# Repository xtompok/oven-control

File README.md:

# Oven control software
Boards and software used to control electric oven

# Installation

 - burn raspbian to SD card
 - create ssh file on boot partition of the SD card
 - `sudo raspi-config`
	- set hostname
	- set password
	- set locale
	- set timezone
	- set read-only
 - `sudo apt update`
 - `sudo apt install vim git python3-venv mosquitto nginx`
 - clone this repo
 - in `oven-control/sw/web_interface`:
	- `python3 -m venv venv`
	- `. venv/bin/activate/`
	- `pip install -r requirements.txt`
 - `mkdir -p .config/systemd/user/`
 - `cp oven_control.service .config/systemd/user/` 
 - `sudo loginctl enable-linger pi`
 - edit `/etc/mosquitto/mosquitto.conf`:

  log_dest stderr

  listener 1883
  protocol mqtt

  listener 9001
  protocol websockets

 - `sudo systemctl restart mosquitto`
 - edit `/etc/nginx/sites-available/default`
	- `root /home/pi/oven-control/sw/web_interface/static/`
 - edit `/etc/nginx/nginx.conf`:
	- add to `http` directive `charset UTF-8;`
 - `sudo systemctl restart nginx`

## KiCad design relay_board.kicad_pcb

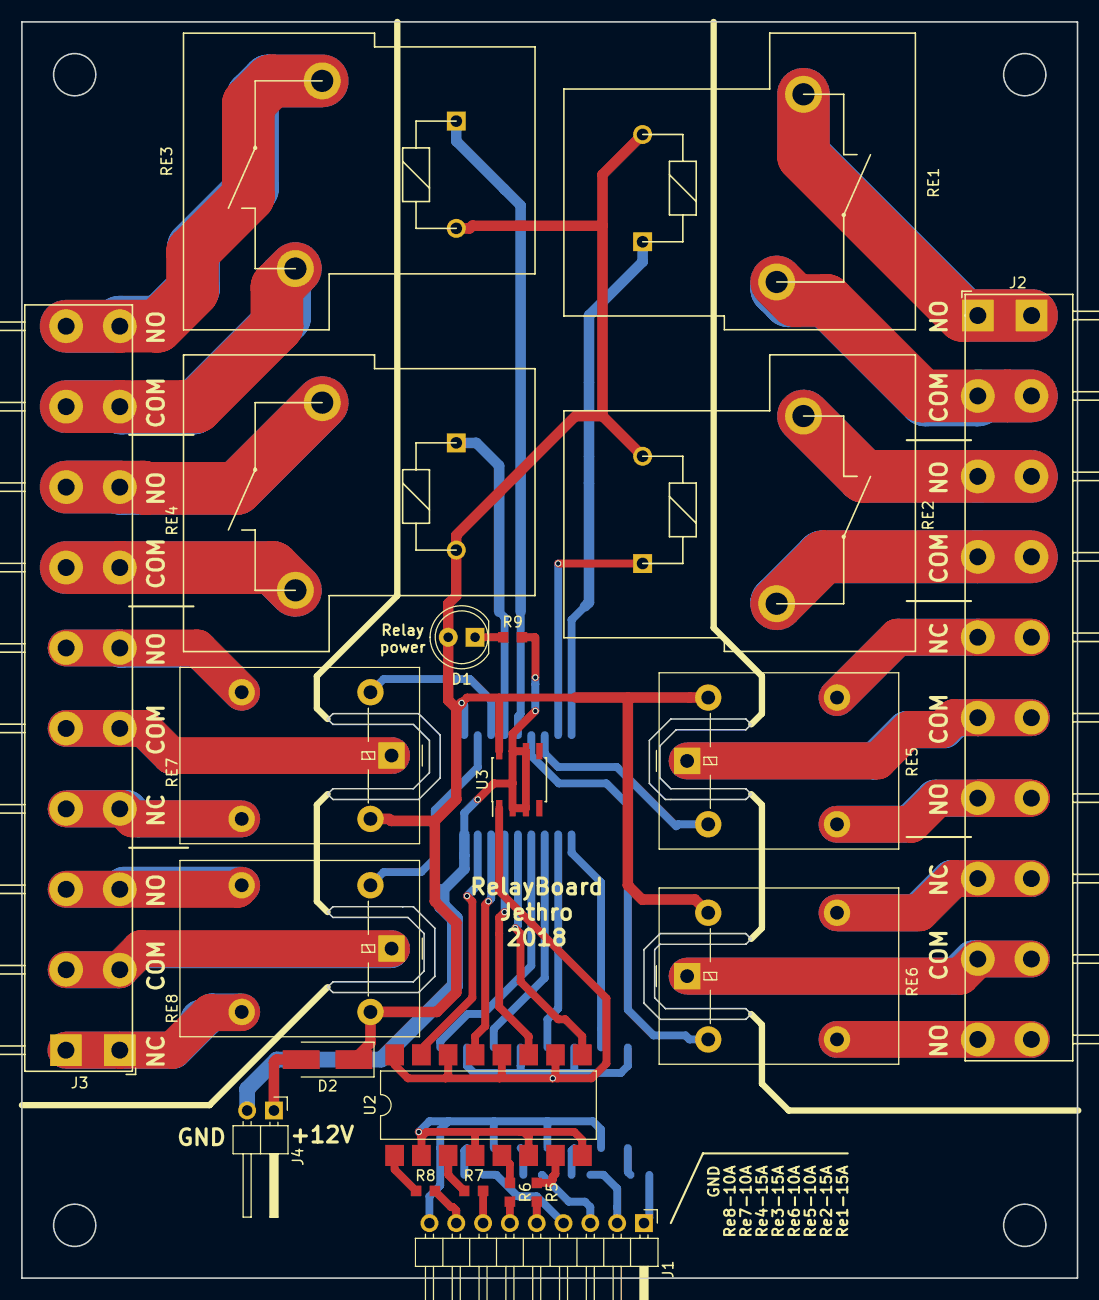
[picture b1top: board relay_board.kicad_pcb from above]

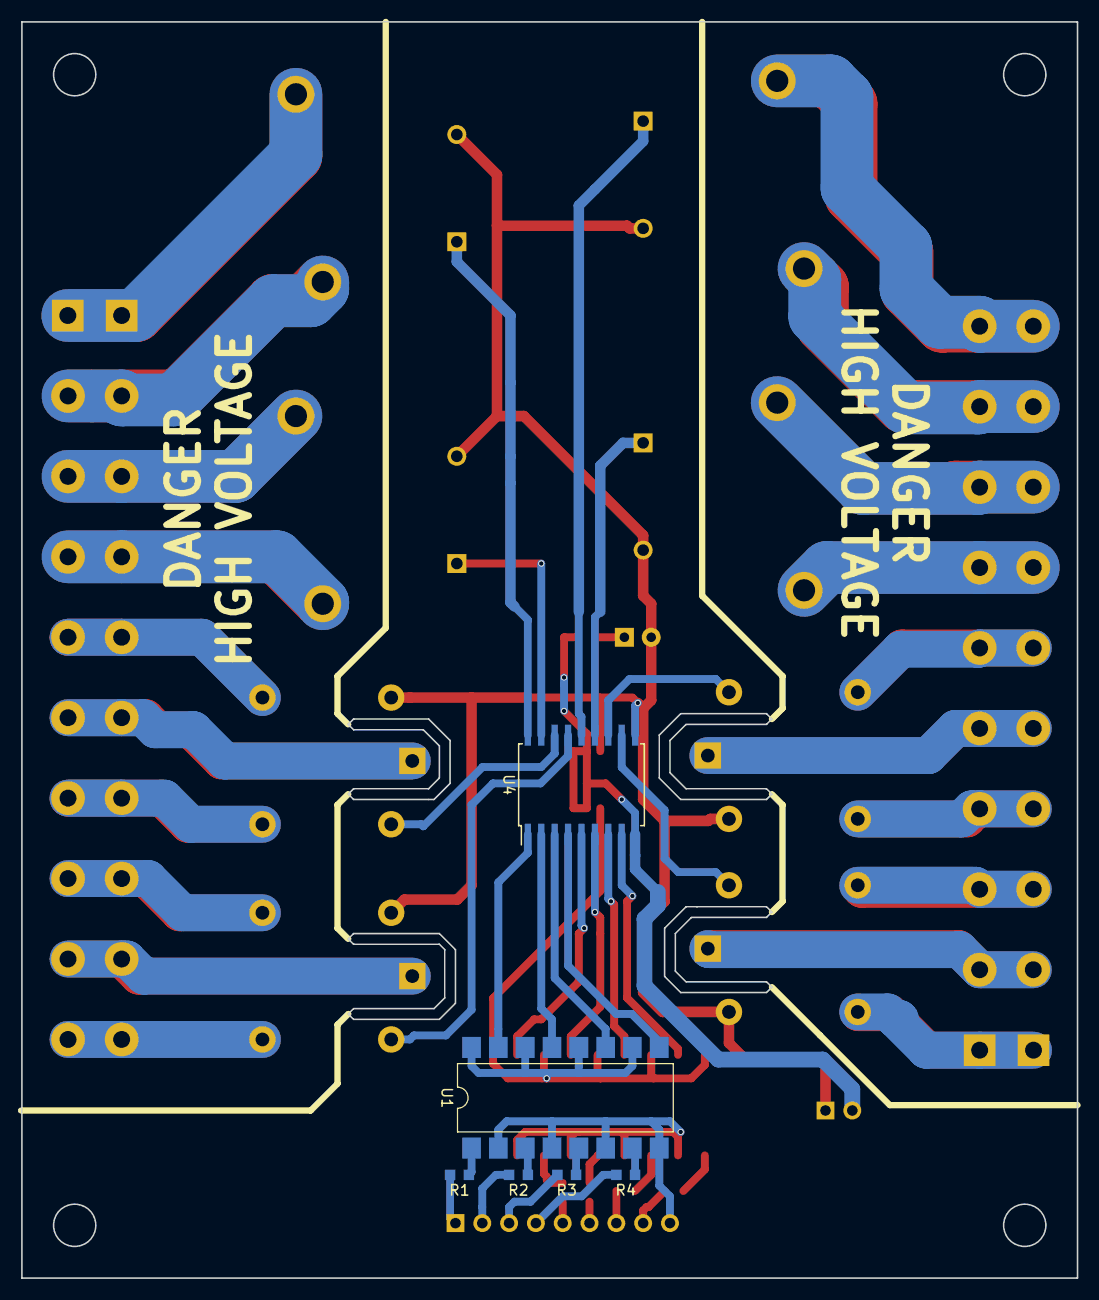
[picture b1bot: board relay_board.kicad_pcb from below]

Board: 2 copper layers, 100.0 x 119.0 mm, 27 parts (6 on the bottom side), 58 nets.

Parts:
D1: LED; LED_D5.0mm
D2: D_Schottky; D_SMA_Handsoldering
J1: Conn_01x09_Male; PinHeader_1x09_P2.54mm_Horizontal
J2, J3: Conn_01x10_Male; Faston_1x10_P7.62mm_Horizontal
J4: Conn_01x02_Male; PinHeader_1x02_P2.54mm_Horizontal
R1, R2, R3, R4, R5, R6, R7, R8, R9: R; R_0603_1608Metric_Pad0.99x1.00mm_HandSolder
RE1, RE2, RE3, RE4: G5Q-1A; Relay_SPST_Hongfa_HF105F1
RE5, RE6, RE7, RE8: G5LE-1; Relay_SPDT_Omron-G5LE-1
U1, U2: LTV-847; SMDIP-16_W9.53mm
U3: L78L05_SO8; SOIC-8_3.9x4.9mm_P1.27mm
U4: ULN2803A; SOIC-18W_7.5x11.6mm_P1.27mm

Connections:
+5VP: U1.10, U1.12, U1.14, U1.16, U2.10, U2.12, U2.14, U2.16, U3.1
+12V: D1.2, D2.1, RE1.5, RE2.5, RE3.5, RE4.5, RE5.5, RE6.5, RE7.5, RE8.5, U3.8, U4.10
/R1IN: J2.2, RE1.2
/R1NO: J2.1, RE1.3
/R2IN: J2.3, RE2.3
/R2NO: J2.4, RE2.2
/R3IN: J3.9, RE3.3
/R3NO: J3.10, RE3.2
/R4IN: J3.7, RE4.3
/R4NO: J3.8, RE4.2
/R5IN: J2.6, RE5.1
/R5NC: J2.5, RE5.4
/R5NO: J2.7, RE5.3
/R6IN: J2.9, RE6.1
/R6NC: J2.8, RE6.4
/R6NO: J2.10, RE6.3
/R7IN: J3.5, RE7.1
/R7NC: J3.4, RE7.4
/R7NO: J3.6, RE7.3
/R8IN: J3.2, RE8.1
/R8NC: J3.1, RE8.4
/R8NO: J3.3, RE8.3
GND: J4.2, R9.2, U3.2, U3.3, U3.6, U3.7, U4.9
GNDD: J1.9, U1.2, U1.4, U1.6, U1.8, U2.2, U2.4, U2.6, U2.8
unnamed: D1.1, R9.1
unnamed: D2.2, J4.1
unnamed: J1.1, R1.2
unnamed: J1.2, R2.2
unnamed: J1.3, R3.2
unnamed: J1.4, R4.2
unnamed: J1.5, R5.2
unnamed: J1.6, R6.2
unnamed: J1.7, R7.2
unnamed: J1.8, R8.2
unnamed: R1.1, U1.1
unnamed: R2.1, U1.3
unnamed: R3.1, U1.5
unnamed: R4.1, U1.7
unnamed: R5.1, U2.7
unnamed: R6.1, U2.5
unnamed: R7.1, U2.3
unnamed: R8.1, U2.1
unnamed: RE1.1, U4.18
unnamed: RE2.1, U4.17
unnamed: RE3.1, U4.14
unnamed: RE4.1, U4.13
unnamed: RE5.2, U4.16
unnamed: RE6.2, U4.15
unnamed: RE7.2, U4.12
unnamed: RE8.2, U4.11
unnamed: U1.9, U4.4
unnamed: U1.11, U4.3
unnamed: U1.13, U4.2
unnamed: U1.15, U4.1
unnamed: U2.9, U4.5
unnamed: U2.11, U4.6
unnamed: U2.13, U4.7
unnamed: U2.15, U4.8

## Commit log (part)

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2018-06-03 Added schematic, board withou layout.
2018-06-06 Routed relay board, without finishing.
2018-06-16 Finished board.
2018-06-17 Fixed silkscreen, added metadata to schematic.
2018-10-07 Added simple bang-bang driver with hysteresis.
2018-11-14 Bugfix
2018-12-29 Added arduino sketch, updated driver.
2018-12-30 Added simple web interface
2018-12-30 Unused relay should be off.
2019-01-03 Rewritten backend for webapp.
2019-02-02 AJAX web interface.
2019-11-10 Next big upgrade, using MQTT.
    Backend and frontend now connected using MQTT.
    Frontend in now only static page, Flask is no longer needed.
2019-11-10 Index is no longer template.
2019-11-10 Fixed paths.
2019-11-10 Removed no longer needed files.
2020-04-11 Add hysteresis to door fan switching.
    Door fan now turns off at 45 degrees.
    It still requires 50 degrees to turn on.
    This should counter noise in temperature readings
    and prevent the frequent switching around 50°C.
2020-04-12 Added systemd unit.
2020-04-12 Added installation notes and requirements file
2020-04-12 Fixed IP.
2020-04-12 Improve temperature calculation.
    Measured more data and found a better interpolation.
    Converting to temperature can now fail and throw a ValueError.
    ValueError is currently being caught by DriverWorker.py
    and causes the entire status to not update.
2020-04-12 Fixed wrong indentation.
2020-04-12 Added driver with hysteresis and testing script.
2020-04-14 Fixed IP, fixed concurrent access from more browsers.
